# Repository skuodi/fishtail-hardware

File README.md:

# fishtail-hardware
Hardware designs for the [FishTail wireless ARM debug probe](https://refab.tech/fishtail)

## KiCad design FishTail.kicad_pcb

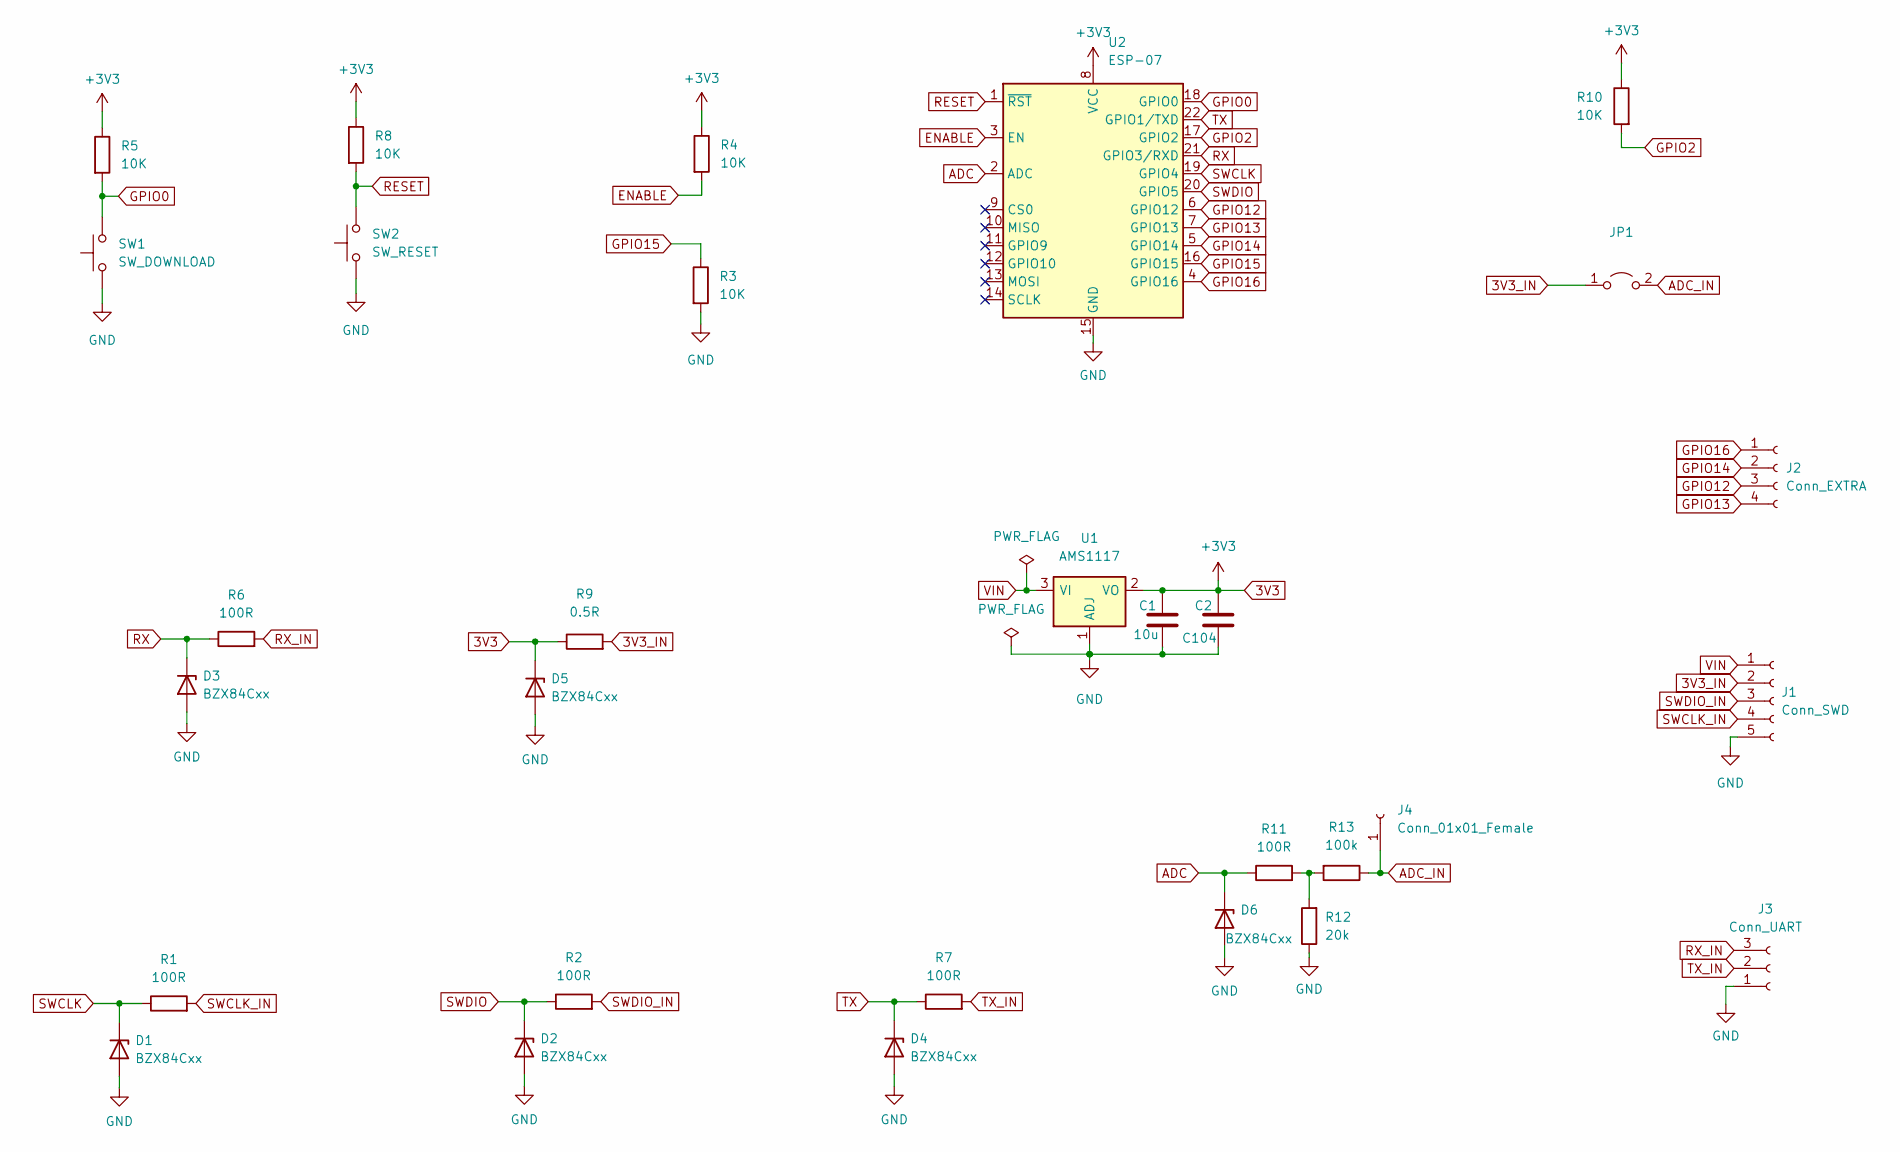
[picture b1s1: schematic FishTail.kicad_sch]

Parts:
C1: 10u; C_0805_2012Metric
C2: C104; C_0805_2012Metric
D1, D2, D3, D4, D5, D6: BZX84Cxx; SOT-23
J1: Conn_SWD; PinSocket_1x05_P2.54mm_Vertical
J2: Conn_EXTRA; PinSocket_1x04_P1.27mm_Vertical
J3: Conn_UART; PinSocket_1x03_P2.54mm_Vertical
J4: Conn_01x01_Female; PinSocket_1x01_P2.54mm_Vertical
JP1: (no value)
R1, R2, R6, R7, R11: 100R; R_0805_2012Metric
R3, R4, R5, R8, R10: 10K; R_0805_2012Metric
R9: 0.5R; R_0805_2012Metric
R12: 20k; R_0805_2012Metric
R13: 100k; R_0805_2012Metric
SW1: SW_DOWNLOAD; SolderJumper-2_P1.3mm_Open_TrianglePad1.0x1.5mm
SW2: SW_RESET; SolderJumper-2_P1.3mm_Open_TrianglePad1.0x1.5mm
U1: AMS1117; SOT-223-3_TabPin2
U2: ESP-07; ESP-12E

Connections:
3V3: C1.1, C2.1, D5.3 (K), R4.1, R5.1, R8.1, R9.1, R10.1, U1.2 (VO), U2.8 (VCC)
3V3_IN: J1.2, JP1.1 (A), R9.2
ADC: D6.3 (K), R11.1, U2.2 (ADC)
ADC_IN: J4.1, JP1.2 (B), R13.1
ENABLE: R4.2, U2.3 (EN)
GND: C1.2, C2.2, D1.1 (A), D2.1 (A), D3.1 (A), D4.1 (A), D5.1 (A), D6.1 (A), J1.5, J3.1, R3.2, R12.1, SW1.1, SW2.1, U1.1 (ADJ), U2.15 (GND)
GPIO0: R5.2, SW1.2, U2.18 (GPIO0)
GPIO2: R10.2, U2.17 (GPIO2)
GPIO12: J2.3, U2.6 (GPIO12)
GPIO13: J2.4, U2.7 (GPIO13)
GPIO14: J2.2, U2.5 (GPIO14)
GPIO15: R3.1, U2.16 (GPIO15)
GPIO16: J2.1, U2.4 (GPIO16)
unnamed: R11.2, R12.2, R13.2
RESET: R8.2, SW2.2, U2.1 (~RST)
RX: D3.3 (K), R6.1, U2.21 (GPIO3/RXD)
RX_IN: J3.3, R6.2
SWCLK: D1.3 (K), R1.1, U2.19 (GPIO4)
SWCLK_IN: J1.4, R1.2
SWDIO: D2.3 (K), R2.1, U2.20 (GPIO5)
SWDIO_IN: J1.3, R2.2
TX: D4.3 (K), R7.1, U2.22 (GPIO1/TXD)
TX_IN: J3.2, R7.2
VIN: J1.1, U1.3 (VI)

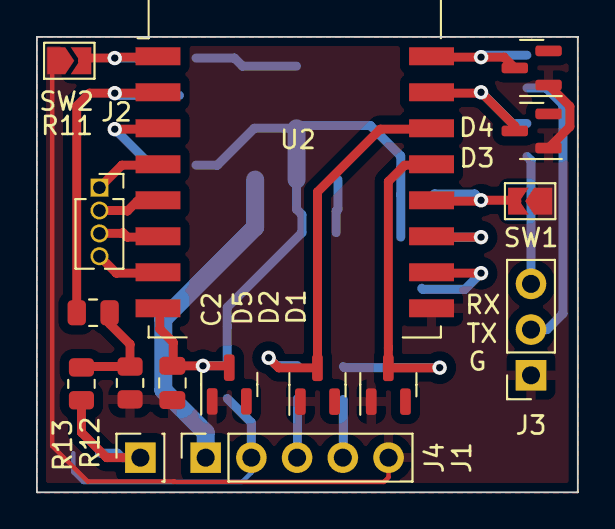
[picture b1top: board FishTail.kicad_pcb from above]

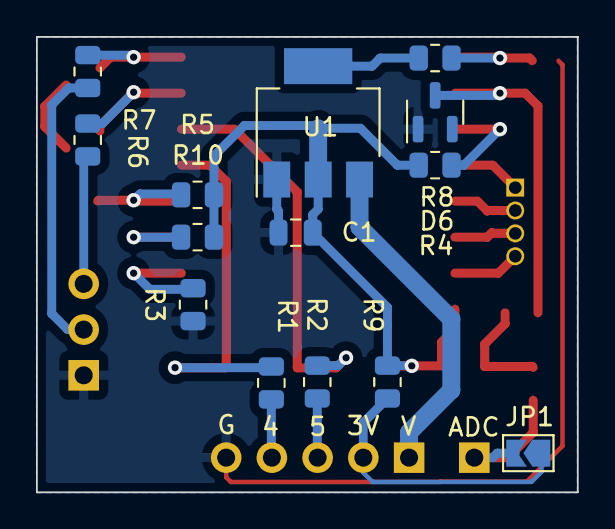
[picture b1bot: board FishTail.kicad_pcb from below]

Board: 2 copper layers, 30.0 x 25.3 mm, 30 parts (14 on the bottom side), 24 nets.
